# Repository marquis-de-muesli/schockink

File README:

NOTE: Schematics+Board are still IN-PROGRESS, i will announce once i am confident enough in them to put them into production myself.

How small can you go while keeping the full power and same (+more) features of a mk-312 box? :)
The answer is about 90x70x35mm, or about 1/8th of the original box.

Much thanks goes to metafetish and the buttshock project where i got started with the schematics.

To save cost and space, the entire control panel with LCD and mechanical buttons had to go.
The idea is to make a bluetooth app to take control instead.

Another major difference is that instead of a simple bluetooth bridge (HC05) i plopped in a whole new powerfull MCU (ESP32) on top of the original hardware.
The reason is twofold.
- The one thing we cant really replace with the ErosLink Protocol is the MA Knob, which is now replaced by a DigPot controlled by our new MCU.
- Eventually the idea is to tinker around with a new firmware from scratch, not just reuse the ET312 one.
  This Design allows to take full control of the Output Stage in the future.

Power will be supplied by 3x 18650 Lithium Cells. 
As of right now i haven't been able to cram in a charging circuit. So for now they are removable and charged in a tabletop charger.
The unintended side effect is that you could keep a spare set of batteries charged.

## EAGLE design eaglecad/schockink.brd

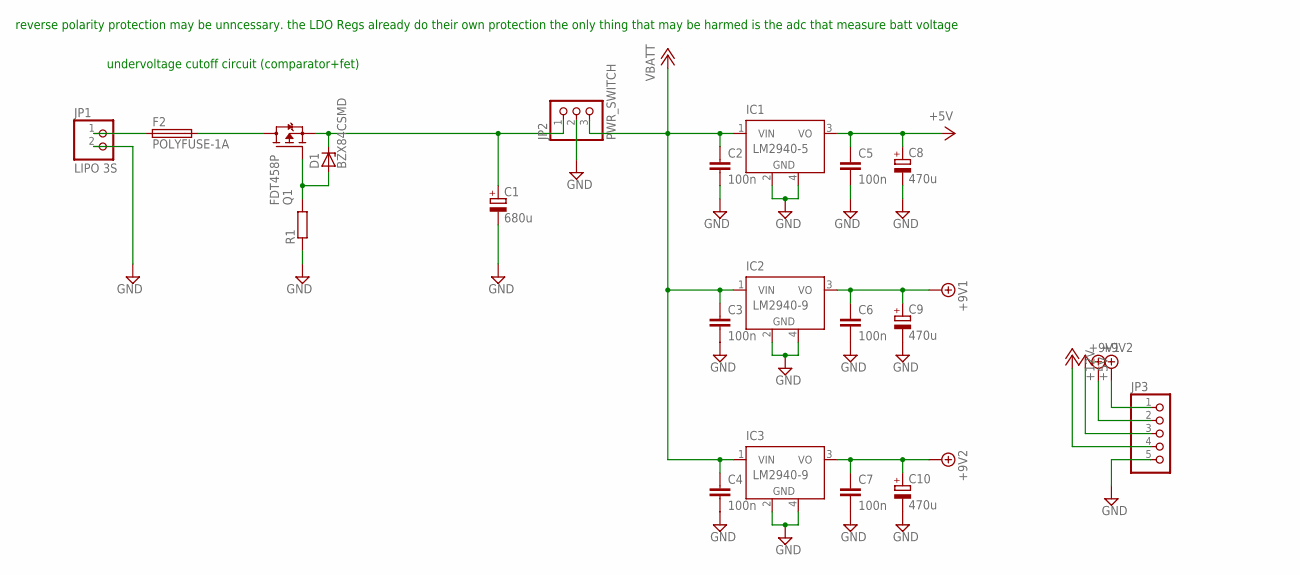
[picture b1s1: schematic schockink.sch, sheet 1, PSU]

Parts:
C1: 680u; UD-8X10_NICHICON
C2, C3, C4, C5, C6, C7: 100n; C2012
C8, C9, C10: 470u; UD-6,3X7,7_NICHICON
D1: BZX84CSMD; TO236
F2: POLYFUSE-1A; R1210
IC1: LM2940-5; SOT223
IC2, IC3: LM2940-9; SOT223
JP1: LIPO 3S; 1X02
JP2: PWR_SWITCH; 1X03
JP3: PINHD-1X5; 1X05
Q1: FDT458P; SOT223; MOUSER# 512-FDT458P
R1: R-EU_M2012; M2012

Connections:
+5V: C5.1, C8.+, IC1.3 (VO), JP3.3; also elsewhere on the board
+9V1: C6.1, C9.+, IC2.3 (VO), JP3.2; also elsewhere on the board
+9V2: C7.1, C10.+, IC3.3 (VO), JP3.1; also elsewhere on the board
+VBATT: C2.1, C3.1, C4.1, IC1.1 (VIN), IC2.1 (VIN), IC3.1 (VIN), JP2.3, JP3.4; also elsewhere on the board
GND: C1.-, C2.2, C3.2, C4.2, C5.2, C6.2, C7.2, C8.-, C9.-, C10.-, IC1.2 (GND), IC1.4 (GND), IC2.2 (GND), IC2.4 (GND), IC3.2 (GND), IC3.4 (GND), JP1.2, JP2.2, JP3.5, R1.1; also elsewhere on the board
unnamed: F2.1, JP1.1
unnamed: F2.2, Q1.2 (D), Q1.4 (D)
unnamed: D1.A, Q1.1 (G), R1.2
unnamed: C1.+, D1.C, JP2.1, Q1.3 (S)

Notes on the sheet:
reverse polarity protection may be unncessary. the LDO Regs already do their own protection the only thing that may be harmed is the adc that measure batt voltage
undervoltage cutoff circuit (comparator+fet)

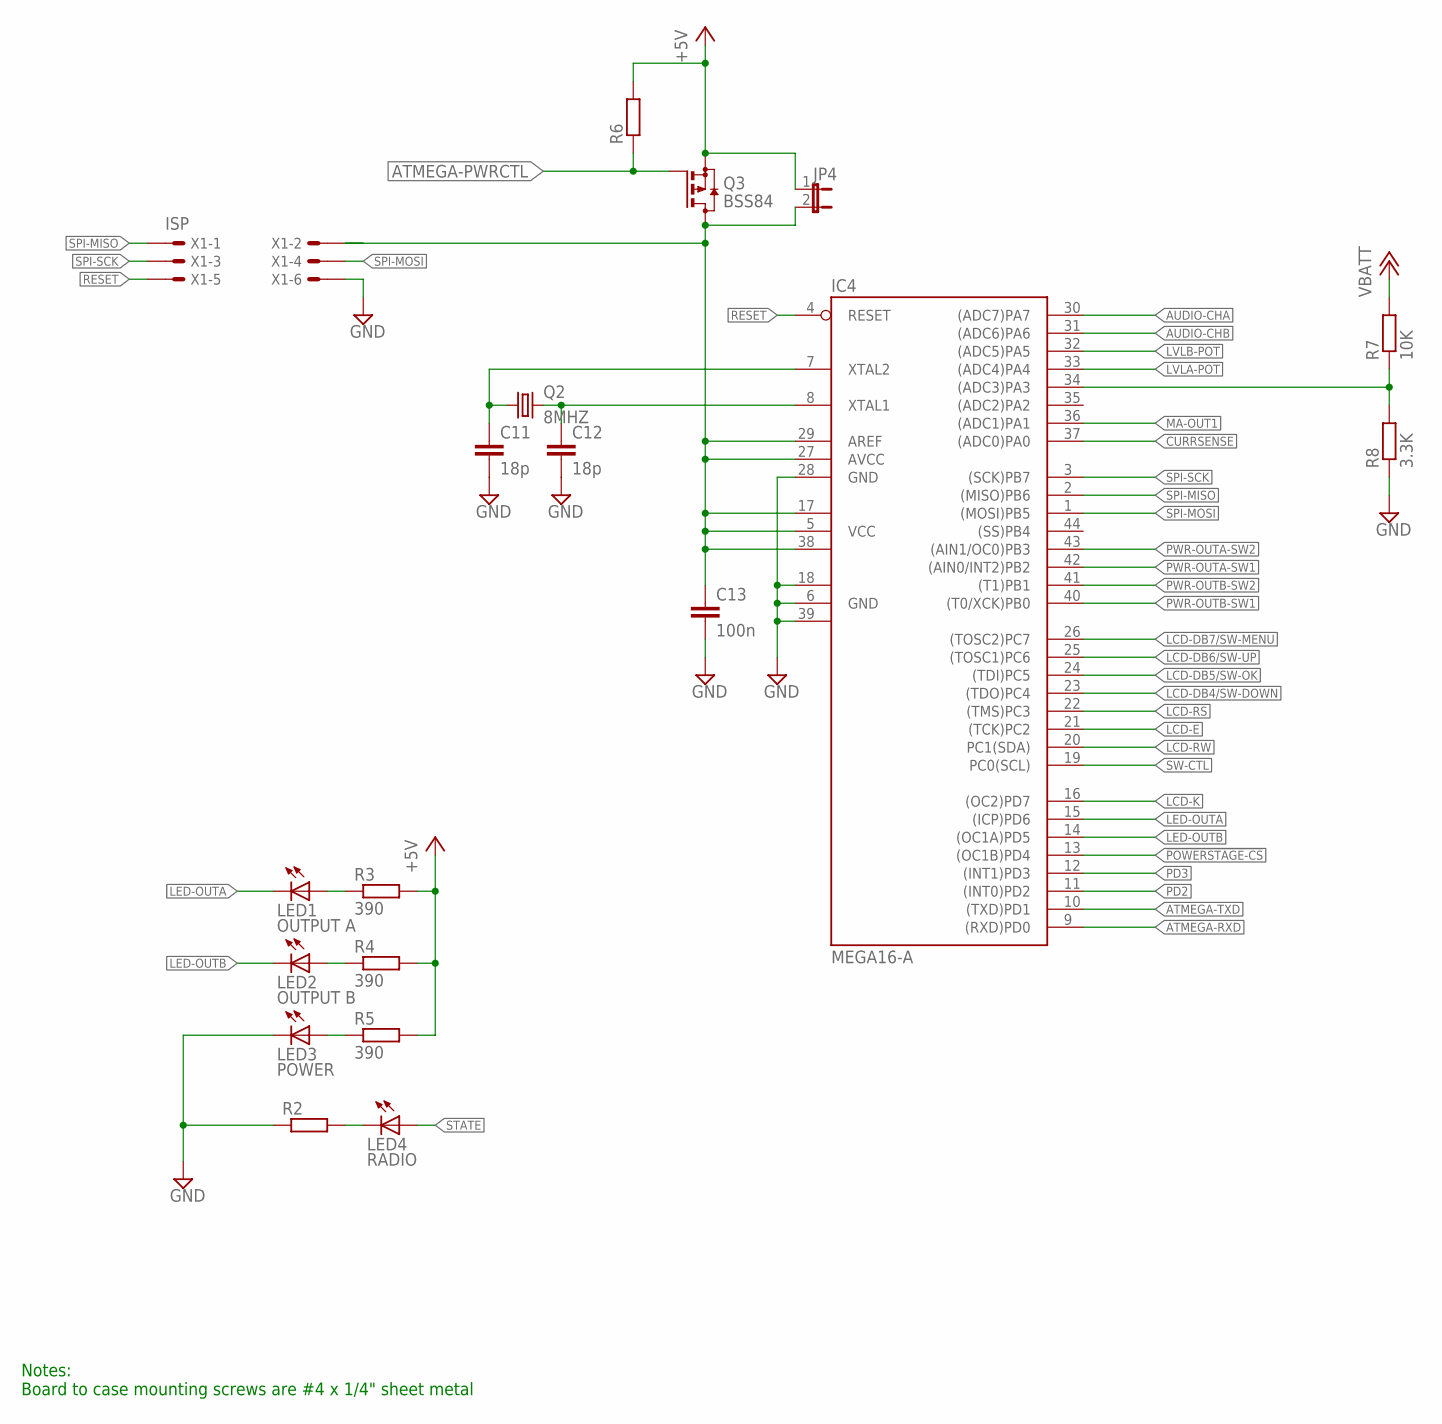
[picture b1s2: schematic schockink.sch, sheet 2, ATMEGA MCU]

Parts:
C11, C12: 18p; C2012
C13: 100n; C2012
IC4: MEGA16-A; TQFP44
JP4: JP1E; JP1
LED1: OUTPUT A; CHIPLED_0805
LED2: OUTPUT B; CHIPLED_0805
LED3: POWER; CHIPLED_0805
LED4: RADIO; CHIPLED_0805
Q2: 8MHZ; CTS406
Q3: BSS84; SOT23
R2, R6: R-EU_M2012; M2012
R3, R4, R5: 390; M2012
R7: 10K; M2012
R8: 3.3K; M2012
X1: ISP; 057-006-1

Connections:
!POWERSTAGE-CS: IC4.13 ((OC1B)PD4); also elsewhere on the board
+5V: JP4.1, Q3.2 (S), R3.2, R4.2, R5.2, R6.2; also elsewhere on the board
+VBATT: R7.2; also elsewhere on the board
ATMEGA-PWRCTL: Q3.1 (G), R6.1; also elsewhere on the board
ATMEGA-RXD: IC4.9 ((RXD)PD0); also elsewhere on the board
ATMEGA-TXD: IC4.10 ((TXD)PD1); also elsewhere on the board
AUDIO-CHA: IC4.30 ((ADC7)PA7); also elsewhere on the board
AUDIO-CHB: IC4.31 ((ADC6)PA6); also elsewhere on the board
CURRSENSE: IC4.37 ((ADC0)PA0); also elsewhere on the board
GND: C11.2, C12.2, C13.2, IC4.6 (GND), IC4.18 (GND1), IC4.28 (GND), IC4.39 (GND2), LED3.C, R2.1, R8.1, X1.6; also elsewhere on the board
LCD-DB4/SW-DOWN: IC4.23 ((TDO)PC4); also elsewhere on the board
LCD-DB5/SW-OK: IC4.24 ((TDI)PC5); also elsewhere on the board
LCD-DB6/SW-UP: IC4.25 ((TOSC1)PC6); also elsewhere on the board
LCD-DB7/SW-MENU: IC4.26 ((TOSC2)PC7); also elsewhere on the board
LCD-E: IC4.21 ((TCK)PC2); also elsewhere on the board
LCD-K: IC4.16 ((OC2)PD7)
LCD-RS: IC4.22 ((TMS)PC3); also elsewhere on the board
LCD-RW: IC4.20 (PC1(SDA))
LED-OUTA: IC4.15 ((ICP)PD6), LED1.C
LED-OUTB: IC4.14 ((OC1A)PD5), LED2.C
LVLA-POT: IC4.33 ((ADC4)PA4)
LVLB-POT: IC4.32 ((ADC5)PA5)
MA-OUT1: IC4.36 ((ADC1)PA1); also elsewhere on the board
unnamed: IC4.34 ((ADC3)PA3), R7.1, R8.2
unnamed: C13.1, IC4.5 (VCC), IC4.17 (VCC1), IC4.27 (AVCC), IC4.29 (AREF), IC4.38 (VCC2), JP4.2, Q3.3 (D), X1.2
unnamed: LED4.C, R2.2
unnamed: C12.1, IC4.8 (XTAL1), Q2.3 (2)
unnamed: LED2.A, R4.1
unnamed: LED1.A, R3.1
unnamed: C11.1, IC4.7 (XTAL2), Q2.1
unnamed: LED3.A, R5.1
PD2: IC4.11 ((INT0)PD2); also elsewhere on the board
PD3: IC4.12 ((INT1)PD3); also elsewhere on the board
PWR-OUTA-SW1: IC4.42 ((AIN0/INT2)PB2); also elsewhere on the board
PWR-OUTA-SW2: IC4.43 ((AIN1/OC0)PB3); also elsewhere on the board
PWR-OUTB-SW1: IC4.40 ((T0/XCK)PB0); also elsewhere on the board
PWR-OUTB-SW2: IC4.41 ((T1)PB1); also elsewhere on the board
RESET: IC4.4 (RESET), X1.5
SPI-MISO: IC4.2 ((MISO)PB6), X1.1
SPI-MOSI: IC4.1 ((MOSI)PB5), X1.4; also elsewhere on the board
SPI-SCK: IC4.3 ((SCK)PB7), X1.3; also elsewhere on the board
STATE: LED4.A; also elsewhere on the board
SW-CTL: IC4.19 (PC0(SCL)); also elsewhere on the board

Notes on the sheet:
Notes: Board to case mounting screws are #4 x 1/4" sheet metal

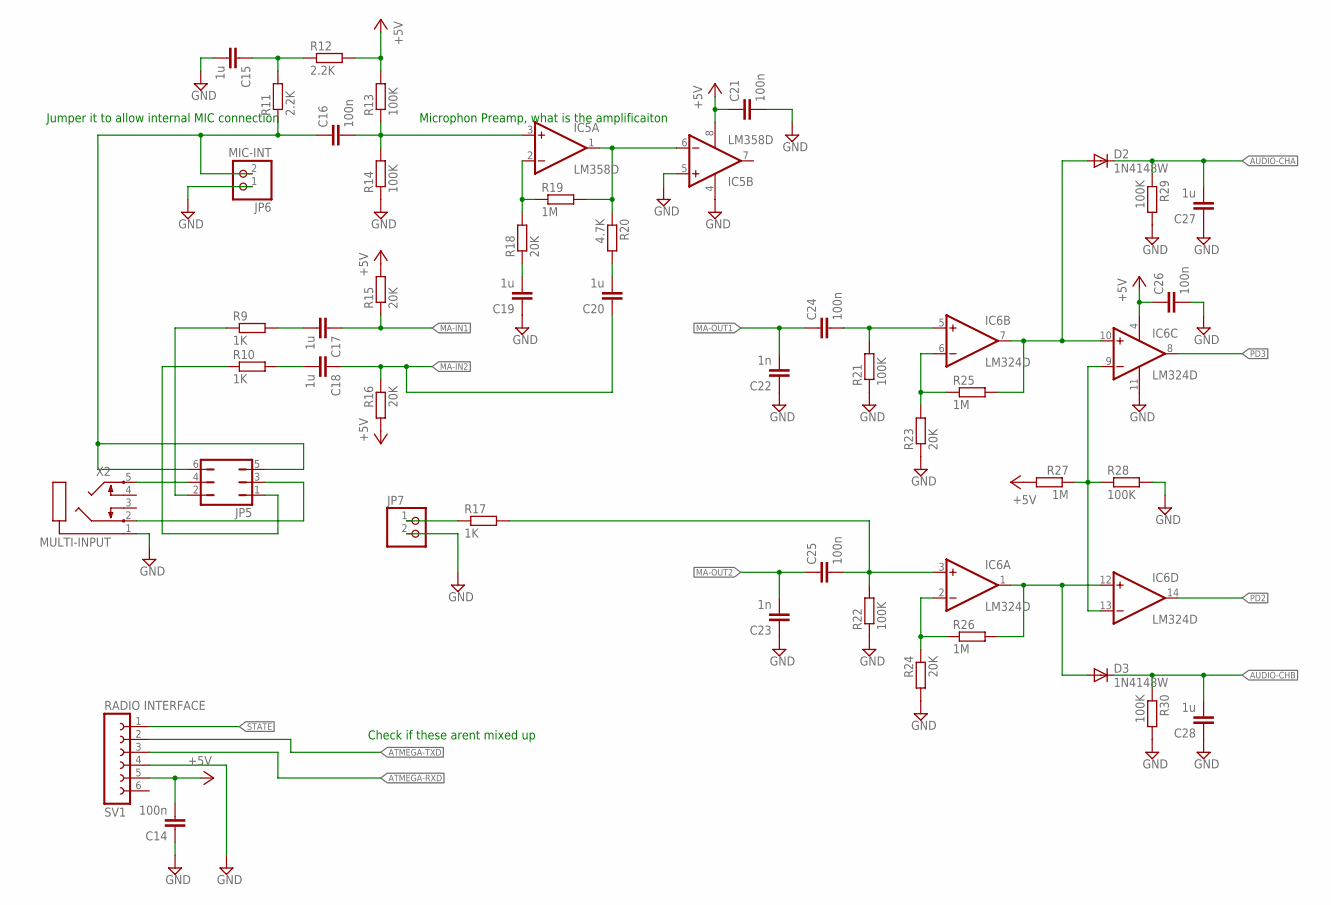
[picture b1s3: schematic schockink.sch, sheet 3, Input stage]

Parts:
C14, C16, C21, C24, C25, C26: 100n; C2012
C15, C17, C18, C19, C20, C27, C28: 1u; C2012
C22, C23: 1n; C2012
D2, D3: 1N4148W; SOD-123_MINI-SMA
IC5: LM358D; SO08
IC6: LM324D; SO14
JP5: JP3Q
JP6: MIC-INT; 1X02
JP7: PINHD-1X2; 1X02
R9, R10, R17: 1K; M2012
R11, R12: 2.2K; M2012
R13, R14, R21, R22, R28, R29, R30: 100K; M2012
R15, R16, R18, R23, R24: 20K; M2012
R19, R25, R26, R27: 1M; M2012
R20: 4.7K; M2012
SV1: RADIO INTERFACE; FE06
X2: MULTI-INPUT; STX3100

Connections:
+5V: C14.2, C21.1, C26.1, IC5.8 (V+), IC6.4 (V+), R12.2, R13.2, R15.2, R16.2, R27.2, SV1.5; also elsewhere on the board
ATMEGA-RXD: SV1.3; also elsewhere on the board
ATMEGA-TXD: SV1.2; also elsewhere on the board
AUDIO-CHA: C27.2, D2.C, R29.1; also elsewhere on the board
AUDIO-CHB: C28.2, D3.C, R30.1; also elsewhere on the board
GND: C14.1, C15.2, C19.1, C21.2, C22.1, C23.1, C26.2, C27.1, C28.1, IC5.4 (V-), IC5.5 (+IN), IC6.11 (V-), JP6.1, JP7.2, R14.1, R21.1, R22.1, R23.1, R24.2, R28.2, R29.2, R30.2, SV1.4, X2.1; also elsewhere on the board
MA-IN1: C17.1, R15.1; also elsewhere on the board
MA-IN2: C18.1, C20.1, R16.1; also elsewhere on the board
MA-OUT1: C22.2, C24.1; also elsewhere on the board
MA-OUT2: C23.2, C25.1; also elsewhere on the board
unnamed: JP7.1, R17.1
unnamed: JP5.4, X2.5
unnamed: JP5.3, X2.2
unnamed: C25.2, IC6.3 (+IN), R17.2, R22.2
unnamed: JP5.2, R9.1
unnamed: JP5.1, R10.1
unnamed: C19.2, R18.1
unnamed: IC6.2 (-IN), R24.1, R26.1
unnamed: D3.A, IC6.1 (OUT), IC6.12 (+IN), R26.2
unnamed: C17.2, R9.2
unnamed: IC6.6 (-IN), R23.2, R25.1
unnamed: IC6.9 (-IN), IC6.13 (-IN), R27.1, R28.1
unnamed: C24.2, IC6.5 (+IN), R21.2
unnamed: C18.2, R10.2
unnamed: D2.A, IC6.7 (OUT), IC6.10 (+IN), R25.2
unnamed: C16.1, JP5.5, JP5.6, JP6.2, R11.1
unnamed: C15.1, R11.2, R12.1
unnamed: C16.2, IC5.3 (+IN), R13.1, R14.2
unnamed: IC5.2 (-IN), R18.2, R19.1
unnamed: IC5.1 (OUT), IC5.6 (-IN), R19.2, R20.1
unnamed: C20.2, R20.2
PD2: IC6.14 (OUT); also elsewhere on the board
PD3: IC6.8 (OUT); also elsewhere on the board
STATE: SV1.1; also elsewhere on the board

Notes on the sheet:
Jumper it to allow internal MIC connection
Check if these arent mixed up
Microphon Preamp, what is the amplificaiton

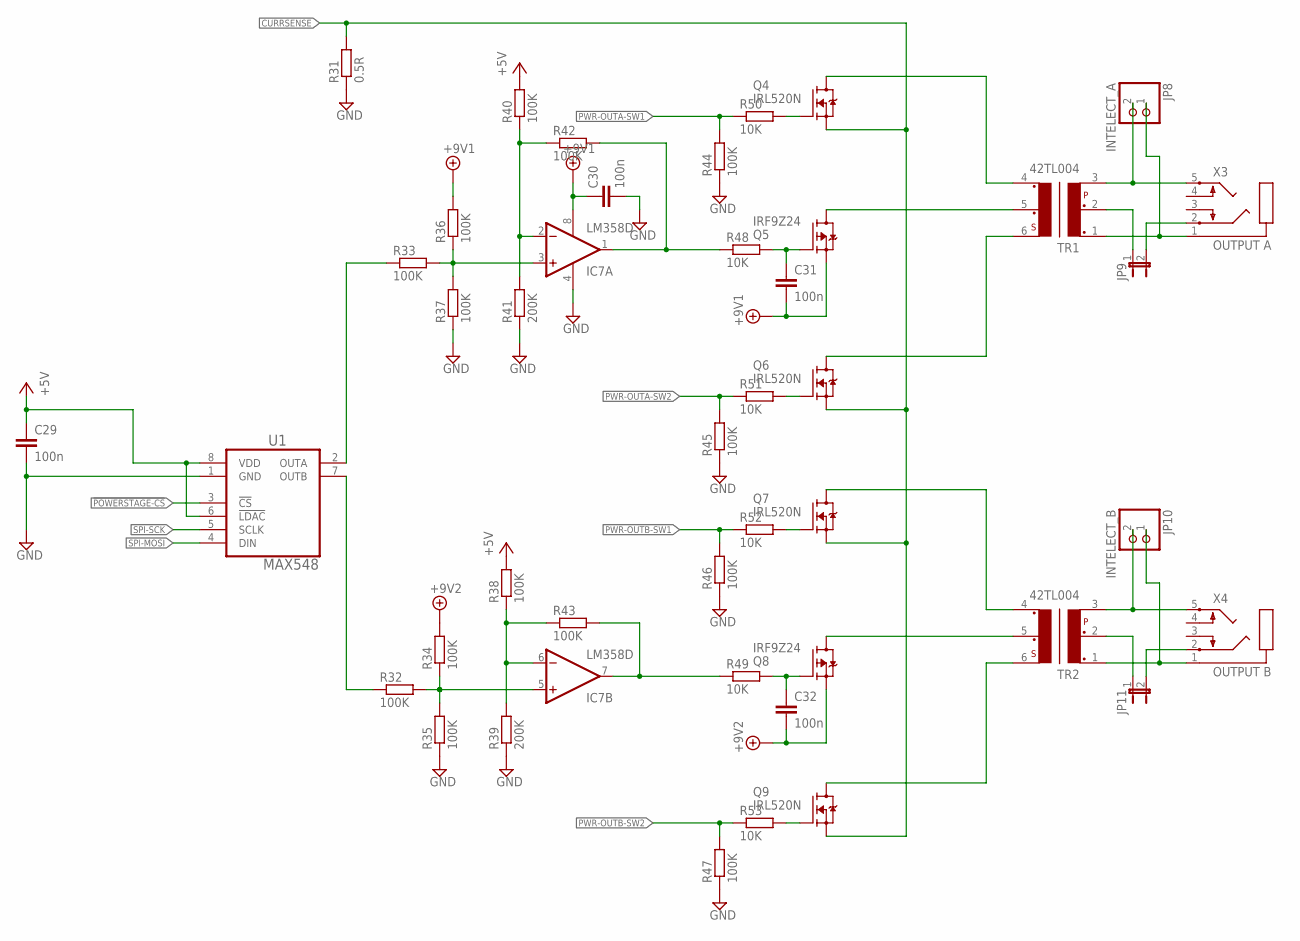
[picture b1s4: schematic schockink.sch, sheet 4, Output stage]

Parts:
C29, C30, C31, C32: 100n; C2012
IC7: LM358D; SO08
JP8: INTELECT_A; 1X02
JP9, JP11: JP1E; JP1
JP10: INTELECT_B; 1X02
Q4, Q6, Q7, Q9: IRL520N; TO263
Q5, Q8: IRF9Z24; TO263
R31: 0.5R; M2012
R32, R33, R34, R35, R36, R37, R38, R40, R42, R43, R44, R45, R46, R47: 100K; M2012
R39, R41: 200K; M2012
R48, R49, R50, R51, R52, R53: 10K; M2012
TR1, TR2: 42TL004; 42TL; MOUSER# 42TL004-RC
U1: MAX548; UMAX8
X3: OUTPUT A; STX3100
X4: OUTPUT B; STX3100

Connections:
!POWERSTAGE-CS: U1.3 (!CS); also elsewhere on the board
+5V: C29.1, R38.2, R40.2, U1.6 (!LDAC), U1.8 (VDD); also elsewhere on the board
+9V1: C30.1, C31.2, IC7.8 (V+), Q5.2 (S), R36.2; also elsewhere on the board
+9V2: C32.2, Q8.2 (S), R34.2; also elsewhere on the board
CURRSENSE: Q4.2 (S), Q6.2 (S), Q7.2 (S), Q9.2 (S), R31.2; also elsewhere on the board
GND: C29.2, C30.2, IC7.4 (V-), R31.1, R35.1, R37.1, R39.1, R41.1, R44.1, R45.1, R46.1, R47.1, U1.1 (GND); also elsewhere on the board
unnamed: Q5.3 (D), TR1.5
unnamed: Q8.3 (D), TR2.5
unnamed: JP11.1, TR2.2
unnamed: JP8.1, TR1.1, X3.1
unnamed: Q4.1 (G), R50.2
unnamed: Q6.1 (G), R51.2
unnamed: JP11.2, X4.2
unnamed: C31.1, Q5.1 (G), R48.2
unnamed: IC7.3 (+IN), R33.2, R36.1, R37.2
unnamed: Q7.1 (G), R52.2
unnamed: Q9.1 (G), R53.2
unnamed: JP10.1, TR2.1, X4.1
unnamed: C32.1, Q8.1 (G), R49.2
unnamed: IC7.5 (+IN), R32.2, R34.1, R35.2
unnamed: Q4.3 (D), TR1.4
unnamed: JP8.2, TR1.3, X3.5
unnamed: Q7.3 (D), TR2.4
unnamed: JP10.2, TR2.3, X4.5
unnamed: Q9.3 (D), TR2.6
unnamed: Q6.3 (D), TR1.6
unnamed: IC7.2 (-IN), R40.1, R41.2, R42.1
unnamed: IC7.6 (-IN), R38.1, R39.2, R43.1
unnamed: R33.1, U1.2 (OUTA)
unnamed: JP9.2, X3.2
unnamed: JP9.1, TR1.2
unnamed: R32.1, U1.7 (OUTB)
PFET_A: IC7.1 (OUT), R42.2, R48.1
PFET_B: IC7.7 (OUT), R43.2, R49.1
PWR-OUTA-SW1: R44.2, R50.1; also elsewhere on the board
PWR-OUTA-SW2: R45.2, R51.1; also elsewhere on the board
PWR-OUTB-SW1: R46.2, R52.1; also elsewhere on the board
PWR-OUTB-SW2: R47.2, R53.1; also elsewhere on the board
SPI-MOSI: U1.4 (DIN); also elsewhere on the board
SPI-SCK: U1.5 (SCLK); also elsewhere on the board

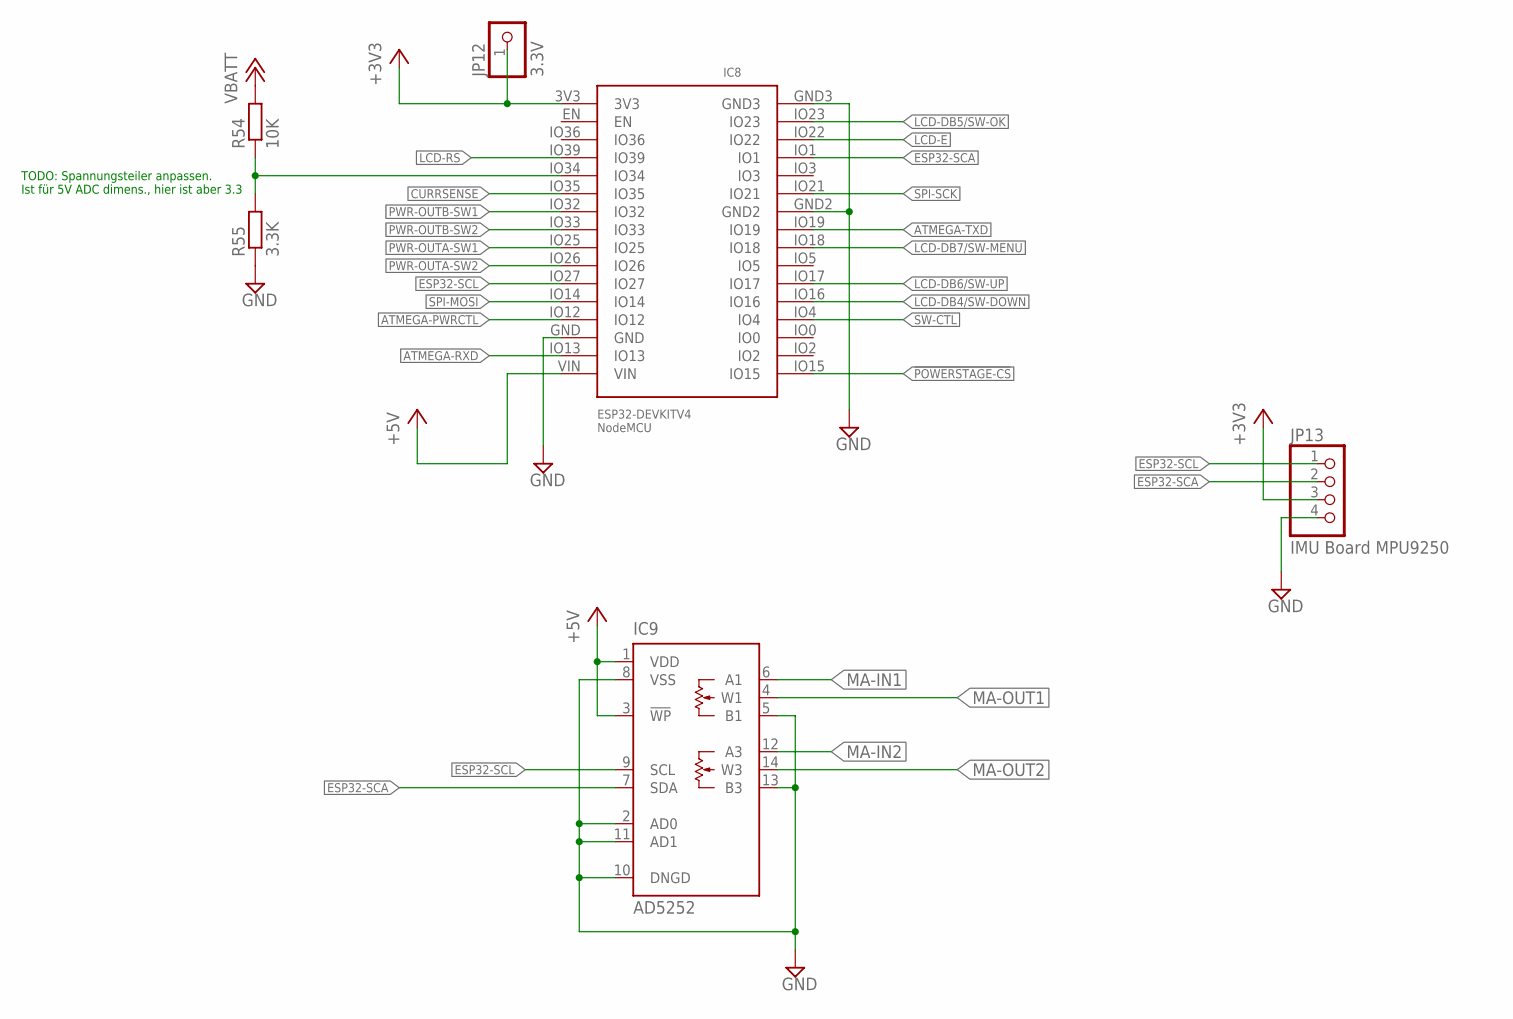
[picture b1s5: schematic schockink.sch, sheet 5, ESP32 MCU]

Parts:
IC8: ESP32DEVKIT; ESP32-DEVKIT
IC9: AD5252; TSSOP14
JP12: 3.3V; 1X01
JP13: IMU Board MPU9250; 1X04
R54: 10K; M2012
R55: 3.3K; M2012

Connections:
!POWERSTAGE-CS: IC8.IO15; also elsewhere on the board
+3V3: IC8.3V3, JP12.1, JP13.3
+5V: IC8.VIN, IC9.1 (VDD), IC9.3 (!WP); also elsewhere on the board
+VBATT: R54.2; also elsewhere on the board
ATMEGA-PWRCTL: IC8.IO12; also elsewhere on the board
ATMEGA-RXD: IC8.IO13; also elsewhere on the board
ATMEGA-TXD: IC8.IO19; also elsewhere on the board
CURRSENSE: IC8.IO35; also elsewhere on the board
ESP32-SCA: IC8.IO1, IC9.7 (SDA), JP13.2
ESP32-SCL: IC8.IO27, IC9.9 (SCL), JP13.1
GND: IC8.GND, IC8.GND2, IC8.GND3, IC9.2 (AD0), IC9.5 (B1), IC9.8 (VSS), IC9.10 (DNGD), IC9.11 (AD1), IC9.13 (B3), JP13.4, R55.1; also elsewhere on the board
LCD-DB4/SW-DOWN: IC8.IO16; also elsewhere on the board
LCD-DB5/SW-OK: IC8.IO23; also elsewhere on the board
LCD-DB6/SW-UP: IC8.IO17; also elsewhere on the board
LCD-DB7/SW-MENU: IC8.IO18; also elsewhere on the board
LCD-E: IC8.IO22; also elsewhere on the board
LCD-RS: IC8.IO39; also elsewhere on the board
MA-IN1: IC9.6 (A1); also elsewhere on the board
MA-IN2: IC9.12 (A3); also elsewhere on the board
MA-OUT1: IC9.4 (W1); also elsewhere on the board
MA-OUT2: IC9.14 (W3); also elsewhere on the board
unnamed: IC8.IO34, R54.1, R55.2
PWR-OUTA-SW1: IC8.IO25; also elsewhere on the board
PWR-OUTA-SW2: IC8.IO26; also elsewhere on the board
PWR-OUTB-SW1: IC8.IO32; also elsewhere on the board
PWR-OUTB-SW2: IC8.IO33; also elsewhere on the board
SPI-MOSI: IC8.IO14; also elsewhere on the board
SPI-SCK: IC8.IO21; also elsewhere on the board
SW-CTL: IC8.IO4; also elsewhere on the board

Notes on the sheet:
TODO: Spannungsteiler anpassen. Ist für 5V ADC dimens., hier ist aber 3.3

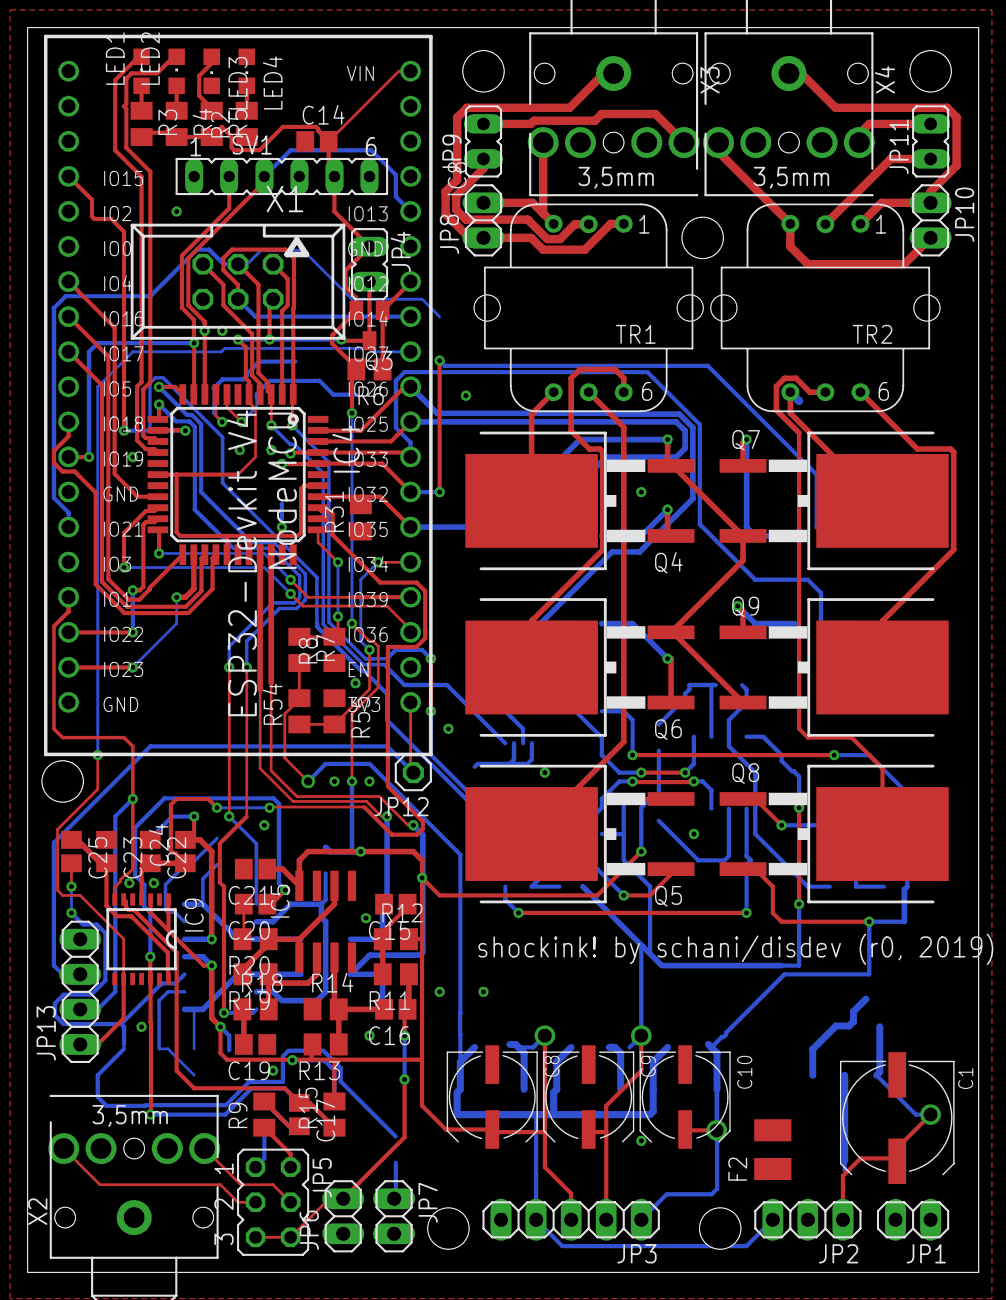
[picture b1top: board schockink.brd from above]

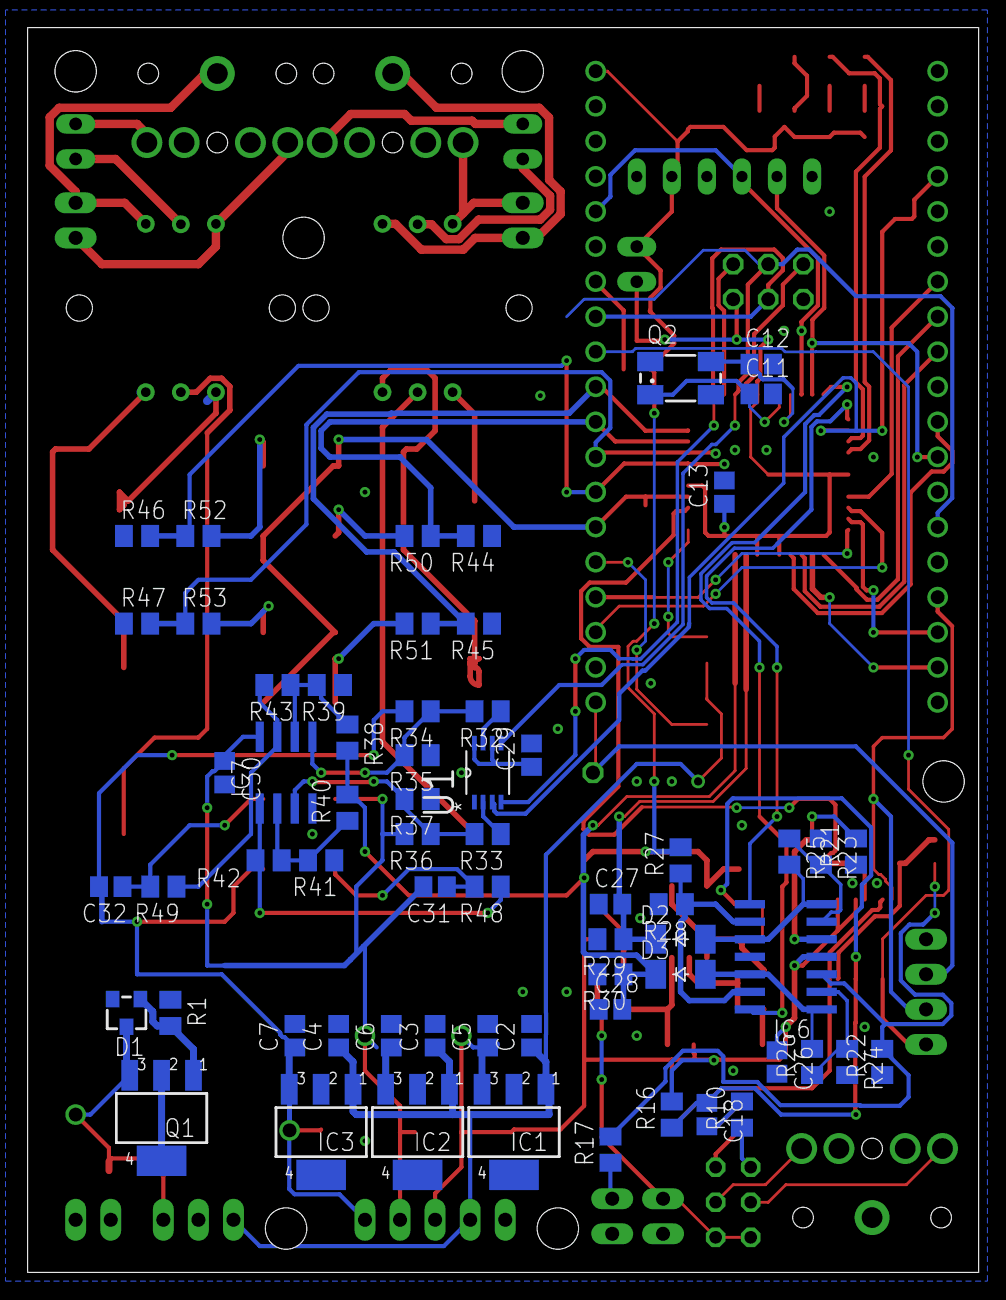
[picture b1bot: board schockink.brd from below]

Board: 2 copper layers, 68.9 x 90.2 mm, 134 parts (64 on the bottom side), 101 nets.

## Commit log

2019-09-21 Initial EagleCAD files *STILL-IN-PROGRESS*
